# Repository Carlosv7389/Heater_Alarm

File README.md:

# Heater Alarm
A small and easy to mount device that turns on a heater in order to warm a room at a specified military time.<br>

## Table of Contents
1. [Demo](#demo)
2. [Built With](#built-with)
3. [Installation](#installation)
4. [Getting Started](#getting-started)
5. [Usage](#usage)
6. [License](#license)
7. [Acknowledgments](#acknowledgments)

## Demo
A Youtube Short testing the Heater Alarm can be found here: <br>

## Built With
IDE: VScode with Platformio extension<br>
MCU: ESP32 wroom wifi devkit V1<br>
Serial Monitoring: Tera Term<br>
Platform: Espressif32<br>
Framework: Adruino<br>

## Installation
* To clone this repository:

    ```bash
    git clone https://github.com/Carlosv7389/Heater_Alarm
    ```

* Download VScode at [this link](https://code.visualstudio.com/download)

    * In the "extension" section find platformio 
    <!--  -->

* Download Tera Term at [this link](https://github.com/TeraTermProject/teraterm/releases)
## Getting Started 
* In VScode, open the folder *Platformio_arduino_wifi*

* Build the circuit shown below:<br>

* To push the code on to the microcontroller, select all code in *main.cpp* and comment it out. The code from the files in the *lib* folder will be pasted into the bottom of the main file and ran before running the actual main code. <br>

## Usage
* Edit the file *include/secrets.h* to change the ssid and password to your wifi ssid and password.
    ```cpp
    // wifi credentials
    const char *ssid = "change to your SSID";
    const char *password = "change to your password";
    ```

* Check Wifi coverage for your microcontroller by running the code found in *lib/WiFi/WIFIScan.cpp*, run Tera Term and check to see if your WiFi SSID is found in the serial terminal ouput, in the image below, my SSID is "CMCKV9803" and so the device is close enough.<br>

* Verify circuit by running the code found in *lib/Blink/Blink.cpp*. When the LED transitions from off to on, the heater should turn on as well as seen in the gif below <br>

* Deploy the original code in the *main.cpp* code by uncommenting and changing the main file in order to match your target time, local timezone, and daylight savings offset.
```cpp
const long gmtOffset_sec = (-5)*3600;  // offset for Central Standard Time in seconds (which is "-5 GMT")
const int daylightOffset_sec = 0; // Offset for daylight savings, set to 0 after changing time in spring, set to 3600 when changing time in the fall. 

// Target time to send activation signal (24-hour format) (currently set to 6:45 AM)
const int TARGET_HOUR = 6;    // 6 hours
const int TARGET_MINUTE = 45;  // 45 minutes
const int TARGET_SECOND = 0;   // 0 seconds
```

Tera Term was used as a serial monitor but can't be used simultaneously while uploading code to the microcontroller, make sure its not active when you upload code.
## License
This project is licensed under the MIT License - see the [LICENSE](LICENSE) file for details.

## Acknowledgments
Huge thanks to the channel [Leo's Bag of Tricks](https://www.youtube.com/@leosbagoftricks3732) for making insightful videos on capacitive touch circuits. The circuit shown in the demo is a THT version of the SMD circuit found [here](https://www.youtube.com/watch?v=V0UkCcv2LmQ)

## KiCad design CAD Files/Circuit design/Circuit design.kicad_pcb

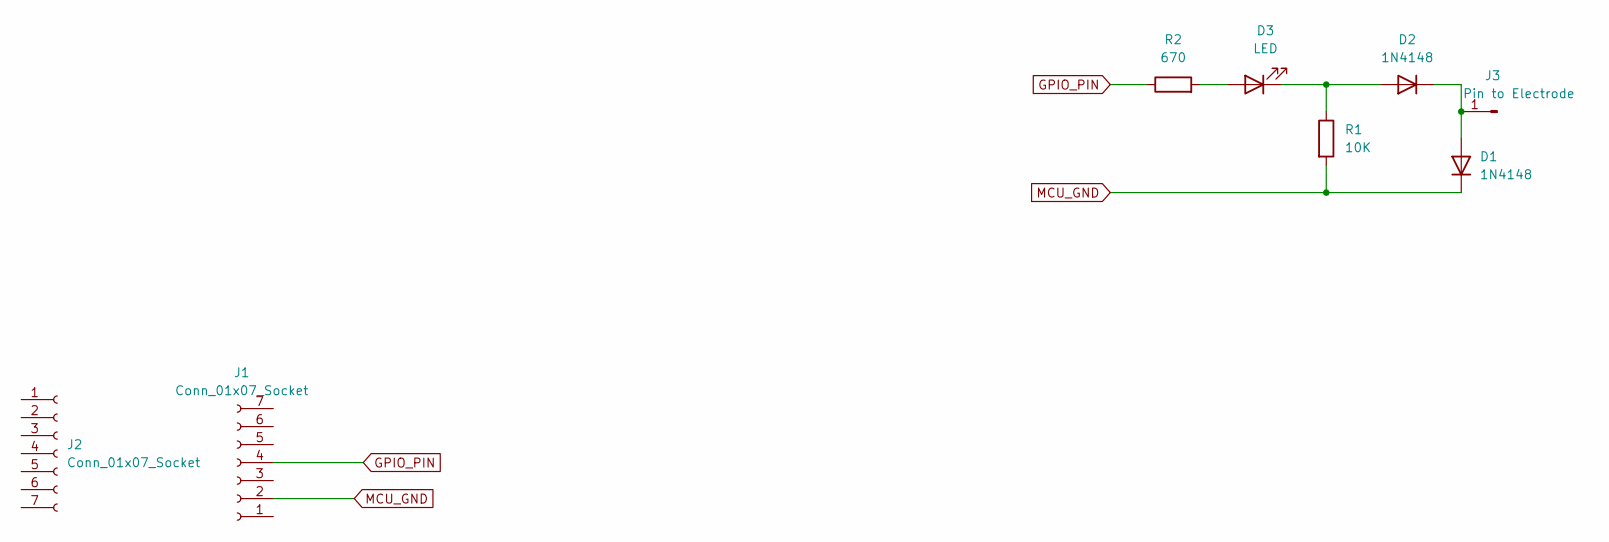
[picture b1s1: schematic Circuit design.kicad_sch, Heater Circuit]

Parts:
D1, D2: 1N4148; D_DO-35_SOD27_P7.62mm_Horizontal
D3: LED; LED_D3.0mm
J1, J2: Conn_01x07_Socket; PinHeader_1x07_P1.27mm_Vertical
J3: Pin to Electrode; PinHeader_1x01_P1.27mm_Vertical
R1: 10K; R_Axial_DIN0204_L3.6mm_D1.6mm_P5.08mm_Horizontal
R2: 670; R_Axial_DIN0204_L3.6mm_D1.6mm_P5.08mm_Horizontal

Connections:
GPIO_PIN: J1.4, R2.1
MCU_GND: D1.1 (K), J1.2, R1.2
unnamed: D1.2 (A), D2.1 (K), J3.1
unnamed: D2.2 (A), D3.1 (K), R1.1
unnamed: D3.2 (A), R2.2

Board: 2 copper layers, 8 parts (0 on the bottom side), 5 nets, no tracks yet.

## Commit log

2026-02-20 Prototype complete, clock reading needs to be more robust
2026-02-23 bug fixed, rtc no longer restarts when waking from sleep mode.
2026-02-26 added .gitignore to ignore personal photos
2026-02-27 adjusted wakeup time to check every minute to avoid double trigger
2026-02-28 Create README.md
    Basic Readme layout set
2026-02-28 Create LICENSE
2026-02-28 Added License note to README
2026-02-28 added media folder
2026-02-28 updated gitignore to not upload videos
2026-03-03 organized files and added to README
2026-03-04 Added to ReadME and added more photos
2026-03-13 Adjusted main.cpp file for daylight savings
2026-03-15 Updated enclosure STL, 3D print passed clearance test
2026-03-15 Uploaded correct enclosure stl file
